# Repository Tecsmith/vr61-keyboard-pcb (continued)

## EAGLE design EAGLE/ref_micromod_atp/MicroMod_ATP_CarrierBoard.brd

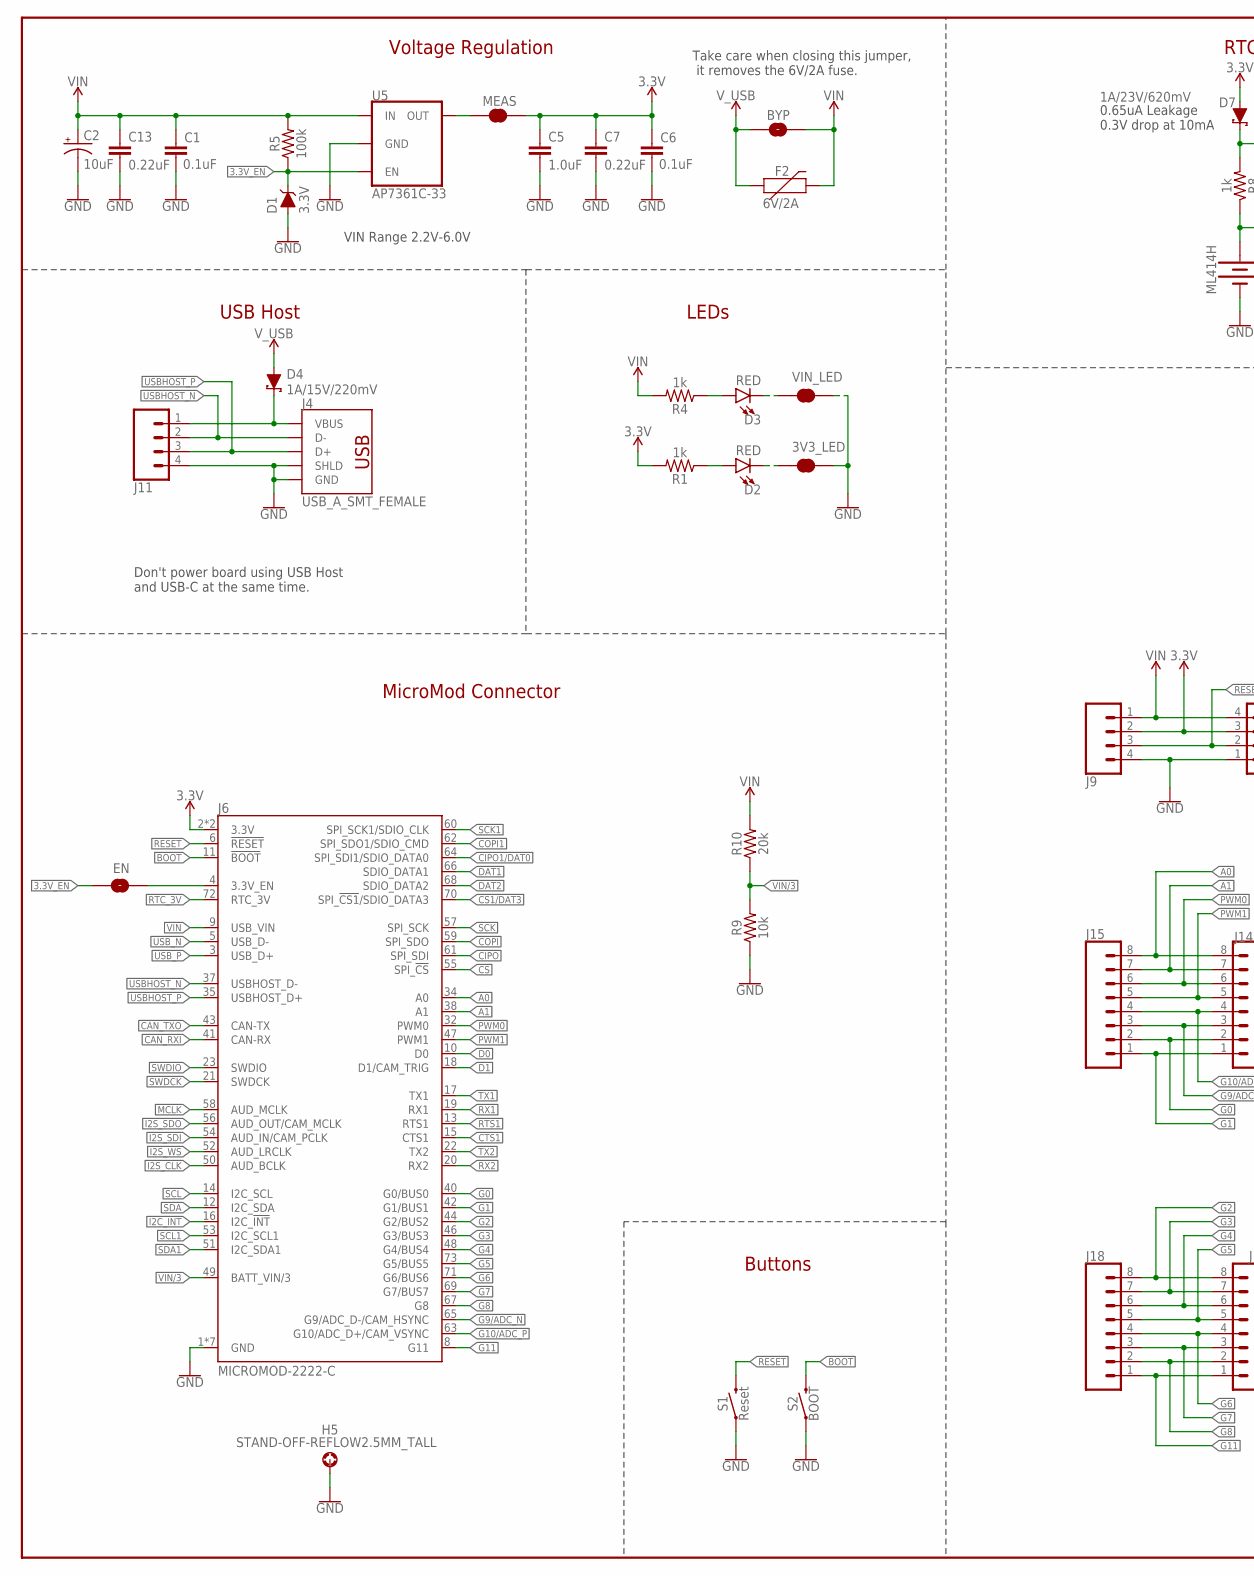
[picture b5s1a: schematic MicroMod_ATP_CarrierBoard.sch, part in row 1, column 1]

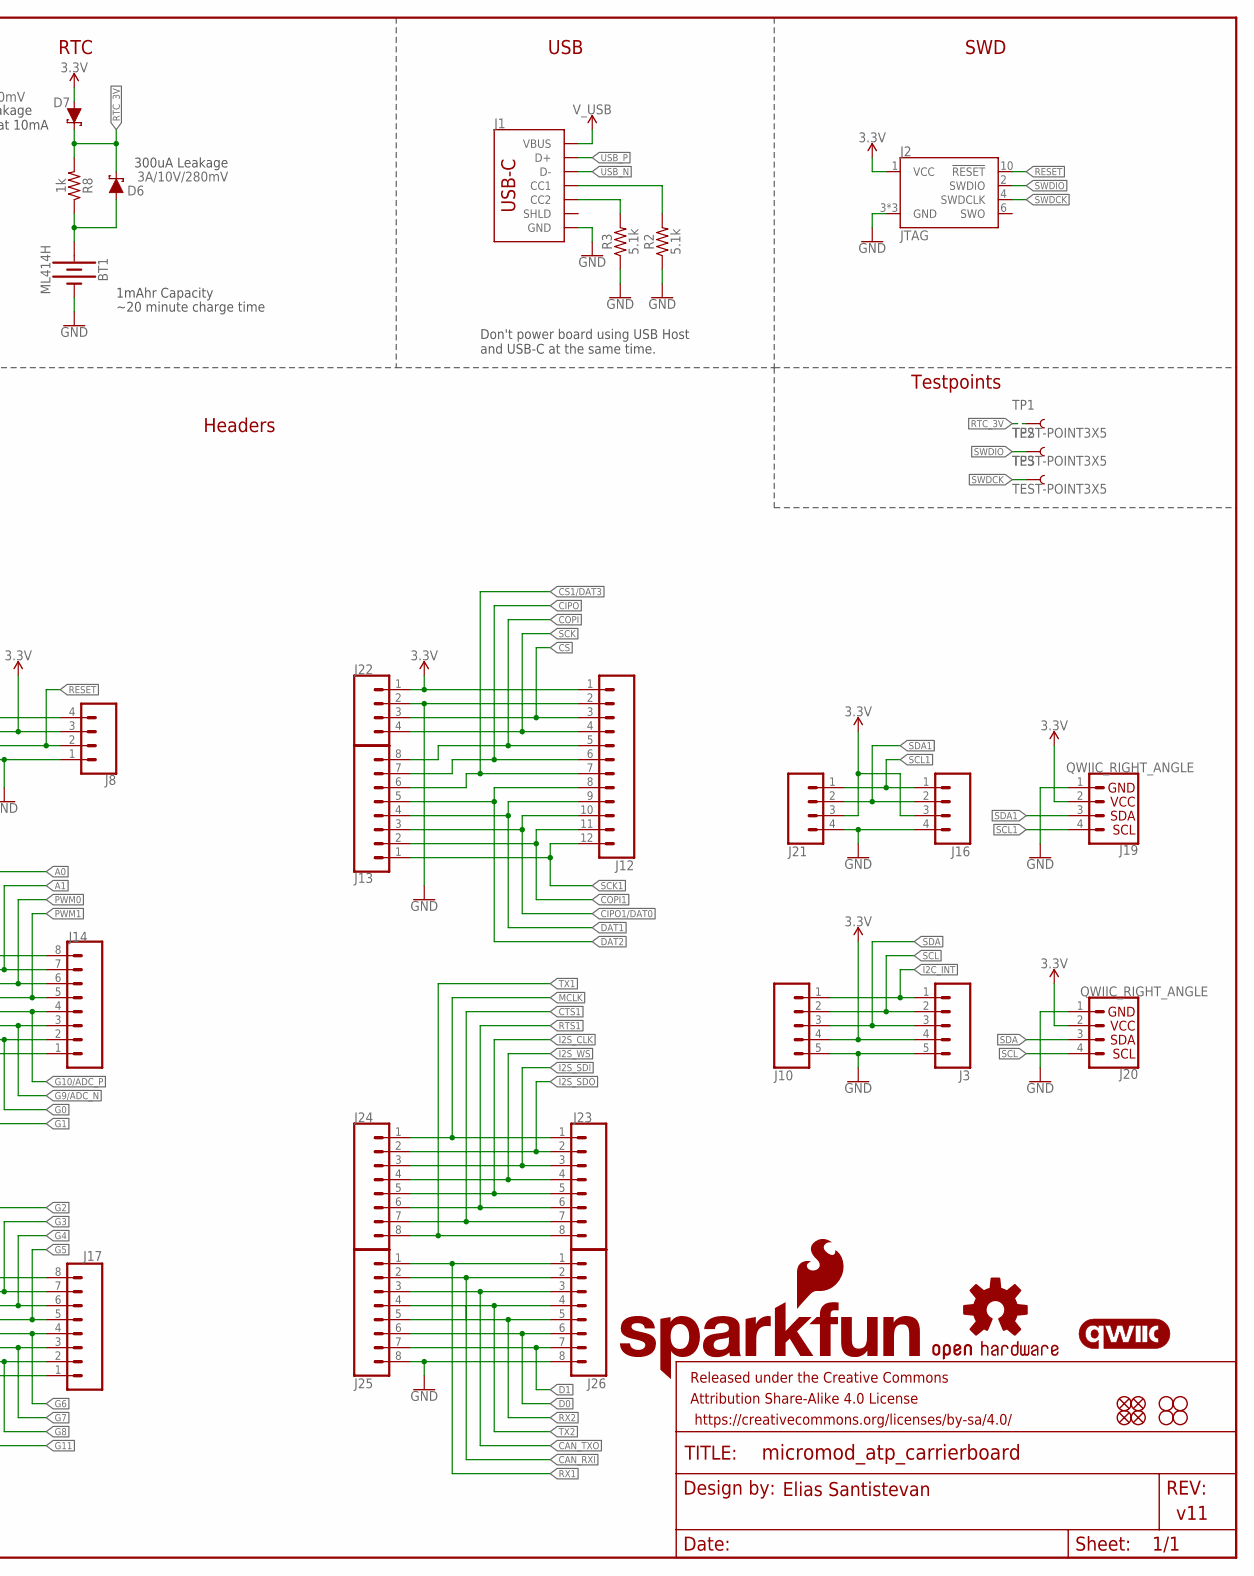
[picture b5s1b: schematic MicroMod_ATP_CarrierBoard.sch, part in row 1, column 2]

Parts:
3V3_LED: JUMPER-SMT_2_NC_TRACE_SILK; SMT-JUMPER_2_NC_TRACE_SILK
BT1: ML414H; ML414H_IV01E
BYP: JUMPER-SMT_2_NO_SILK; SMT-JUMPER_2_NO_SILK
C1, C6: 0.1uF; 0603
C2: 10uF; EIA3216
C5: 1.0uF; 0603
C7, C13: 0.22uF; 0603
D1: 3.3V; SOD-323
D2, D3: RED; LED-0603
D4: 1A/15V/220mV; DO-214BA
D6: 3A/10V/280mV; SOD-323
D7: 1A/23V/620mV; SOD-323
EN: JUMPER-SMT_2_NO_SILK; SMT-JUMPER_2_NO_SILK
F2: 6V/2A; 1210
FD1, FD2, FD3, FD4: FIDUCIALUFIDUCIAL; FIDUCIAL-MICRO
FRAME1: FRAME-LEDGER; CREATIVE_COMMONS
H1, H2, H3, H4: STAND-OFF
H5: STAND-OFF-REFLOW2.5MM_TALL; STAND-OFF-REFLOW-M2.5
J1: USB_C_2-LAYER_PADS; USB-C-16P-2LAYER-PADS
J2: JTAG; 2X5-PTH-1.27MM
J3: CONN_05NO_SILK; 1X05_NO_SILK
J4: USB_A_SMT_FEMALE; USB-A-S-SILK-FEMALE
J6: MICROMOD-2222-C; M.2-CONNECTOR-E
J8, J21: 1X04_SMD_STRAIGHT_COMBO; 1X04_SMD_VERTICAL_COMBO
J9: CONN_041X04_NO_SILK; 1X04_NO_SILK
J10: CONN_05VERT_FEMALE_HEADER; 1X05_SMD_VERTICAL_COMBO
J11, J16, J22: CONN_041X04_NO_SILK_NO_POP; 1X04_NO_SILK
J12: CONN_12SMD_COMBINED; 1X12_SMD_COMBINED
J13: CONN_08NO_SILK_DNP; 1X08_NO_SILK
J14, J17, J24, J25: CONN_08SMD-COMBO-FEMALE; 1X08_SMD_COMBINED
J15, J18, J23, J26: CONN_08NO_SILK_FEMALE_PTH; 1X08_NO_SILK
J19, J20: QWIIC_RIGHT_ANGLE; JST04_1MM_RA
LOGO1: SFE_LOGO_NAME_FLAME.1_INCH; SFE_LOGO_NAME_FLAME_.1
LOGO2: QWIIC_LOGO_5MM; QWIIC_5MM
LOGO3: OSHW-LOGOMINI; OSHW-LOGO-MINI
MEAS: JUMPER-COMBO_2_NC_TRACE; COMBO-JUMPER_2_NC_TRACE
R1, R4, R8: 1k; 0603
R2, R3: 5.1k; 0603
R5: 100k; 0603
R9: 10k; 0603
R10: 20k; 0603
S1: Reset; TACTILE_SWITCH_SMD_5.2MM
S2: BOOT; TACTILE_SWITCH_SMD_5.2MM
TP1, TP2, TP3: TEST-POINT3X5; PAD.03X.05
U5: AP7361C-33; UDFN-8
VIN_LED: JUMPER-SMT_2_NC_TRACE_SILK; SMT-JUMPER_2_NC_TRACE_SILK

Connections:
3.3V: C5.1, C6.1, C7.1, D7.A, J2.1 (VCC), J3.4, J6.2 (3.3V), J6.74 (3.3V), J8.3, J9.2, J10.4, J12.1, J16.3, J19.2, J20.2, J21.3, J22.1, MEAS.2, MEAS.4 (2), R1.2
3.3V_EN: D1.C, EN.1, R5.1, U5.5 (EN)
!BOOT!: J6.11 (!BOOT!), S2.3 (2), S2.4 (2)
!CS1!/DAT3: J6.70 (SPI_!CS1!/SDIO_DATA3), J12.7, J13.6
!CS!: J6.55 (SPI_!CS!), J12.3, J22.3
!RESET: J2.10 (!RESET), J6.6 (!RESET!), J8.2, J9.3, S1.3 (2), S1.4 (2)
A0: J6.34 (A0), J14.8, J15.8
A1: J6.38 (A1), J14.7, J15.7
CAN_RXI: J6.41 (CAN-RX), J25.2, J26.2
CAN_TXO: J6.43 (CAN-TX), J25.3, J26.3
CIPO: J6.61 (SPI_SDI), J12.6, J13.7
CIPO1/DAT0: J6.64 (SPI_SDI1/SDIO_DATA0), J12.10, J13.3
COPI: J6.59 (SPI_SDO), J12.5, J13.8
COPI1: J6.62 (SPI_SDO1/SDIO_CMD), J12.11, J13.2
CTS1: J6.15 (CTS1), J23.7, J24.7
D0: J6.10 (D0), J25.6, J26.6
D1: J6.18 (D1/CAM_TRIG), J25.7, J26.7
DAT1: J6.66 (SDIO_DATA1), J12.9, J13.4
DAT2: J6.68 (SDIO_DATA2), J12.8, J13.5
G0: J6.40 (G0/BUS0), J14.2, J15.2
G1: J6.42 (G1/BUS1), J14.1, J15.1
G2: J6.44 (G2/BUS2), J17.8, J18.8
G3: J6.46 (G3/BUS3), J17.7, J18.7
G4: J6.48 (G4/BUS4), J17.6, J18.6
G5: J6.73 (G5/BUS5), J17.5, J18.5
G6: J6.71 (G6/BUS6), J17.4, J18.4
G7: J6.69 (G7/BUS7), J17.3, J18.3
G8: J6.67 (G8), J17.2, J18.2
G9/ADC_N: J6.65 (G9/ADC_D-/CAM_HSYNC), J14.3, J15.3
G10/ADC_P: J6.63 (G10/ADC_D+/CAM_VSYNC), J14.4, J15.4
G11: J6.8 (G11), J17.1, J18.1
GND: 3V3_LED.2, BT1.-, C1.2, C2.-, C5.2, C6.2, C7.2, C13.2, D1.A, H5.1, J1.GND, J1.GND2 (GND), J2.3 (GND), J2.5 (GND), J2.9 (GND), J3.5, J4.GND, J4.SHLD1 (SHLD), J4.SHLD2 (SHLD), J6.1 (GND), J6.7 (GND), J6.33 (GND), J6.36 (GND), J6.39 (GND), J6.45 (GND), J6.75 (GND), J8.1, J9.4, J10.5, J11.4, J12.2, J16.4, J19.1, J20.1, J21.4, J22.2, J25.8, J26.8, R2.1, R3.1, R9.1, S1.1, S1.2 (1), S2.1, S2.2 (1), U5.4 (GND), U5.EP (GND), VIN_LED.2
I2C_!INT: J3.1, J6.16 (I2C_!INT!), J10.1
I2S_CLK: J6.50 (AUD_BCLK), J23.5, J24.5
I2S_SDI: J6.54 (AUD_IN/CAM_PCLK), J23.3, J24.3
I2S_SDO: J6.56 (AUD_OUT/CAM_MCLK), J23.2, J24.2
I2S_WS: J6.52 (AUD_LRCLK), J23.4, J24.4
MCLK: J6.58 (AUD_MCLK), J23.1, J24.1
unnamed: D2.A, R1.1
unnamed: D3.A, R4.1
unnamed: 3V3_LED.1, D2.C
unnamed: D3.C, VIN_LED.1
unnamed: EN.2, J6.4 (3.3V_EN)
unnamed: D4.C, J4.VBUS, J11.1
unnamed: J1.A5 (CC1), R2.2
unnamed: J1.B5 (CC2), R3.2
unnamed: BT1.+, D6.A, R8.1
OUT_MEAS: MEAS.1, MEAS.3 (1), U5.1 (OUT)
PWM0: J6.32 (PWM0), J14.6, J15.6
PWM1: J6.47 (PWM1), J14.5, J15.5
RTC_3V: D6.C, D7.C, J6.72 (RTC_3V), R8.2, TP1.P$1
RTS1: J6.13 (RTS1), J23.6, J24.6
RX1: J6.19 (RX1), J25.1, J26.1
RX2: J6.20 (RX2), J25.5, J26.5
SCK: J6.57 (SPI_SCK), J12.4, J22.4
SCK1: J6.60 (SPI_SCK1/SDIO_CLK), J12.12, J13.1
SCL: J3.2, J6.14 (I2C_SCL), J10.2, J20.4
SCL1: J6.53 (I2C_SCL1), J16.1, J19.4, J21.1
SDA: J3.3, J6.12 (I2C_SDA), J10.3, J20.3
SDA1: J6.51 (I2C_SDA1), J16.2, J19.3, J21.2
SWDCK: J2.4 (SWDCLK), J6.21 (SWDCK), TP3.P$1
SWDIO: J2.2 (SWDIO), J6.23 (SWDIO), TP2.P$1
TX1: J6.17 (TX1), J23.8, J24.8
TX2: J6.22 (TX2), J25.4, J26.4
USBHOST_N: J4.D-, J6.37 (USBHOST_D-), J11.2
USBHOST_P: J4.D+, J6.35 (USBHOST_D+), J11.3
USB_N: J1.A7 (D-), J1.B7 (D-), J6.5 (USB_D-)
USB_P: J1.A6 (D+), J1.B6 (D+), J6.3 (USB_D+)
VIN: BYP.2, C1.1, C2.+, C13.1, F2.2, J6.9 (USB_VIN), J8.4, J9.1, R4.2, R5.2, R10.2, U5.8 (IN)
VIN/3: J6.49 (BATT_VIN/3), R9.2, R10.1
V_USB: BYP.1, D4.A, F2.1, J1.VBUS1 (VBUS), J1.VBUS2 (VBUS)

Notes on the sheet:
300uA Leakage
0.65uA Leakage 0.3V drop at 10mA
~20 minute charge time
1mAhr Capacity
Take care when closing this jumper, it removes the 6V/2A fuse.
SWD
USB
Headers
RTC
Voltage Regulation
MicroMod Connector
Elias Santistevan
LEDs
USB Host
Buttons
v11
VIN Range 2.2V-6.0V
Don't power board using USB Host and USB-C at the same time.
Testpoints

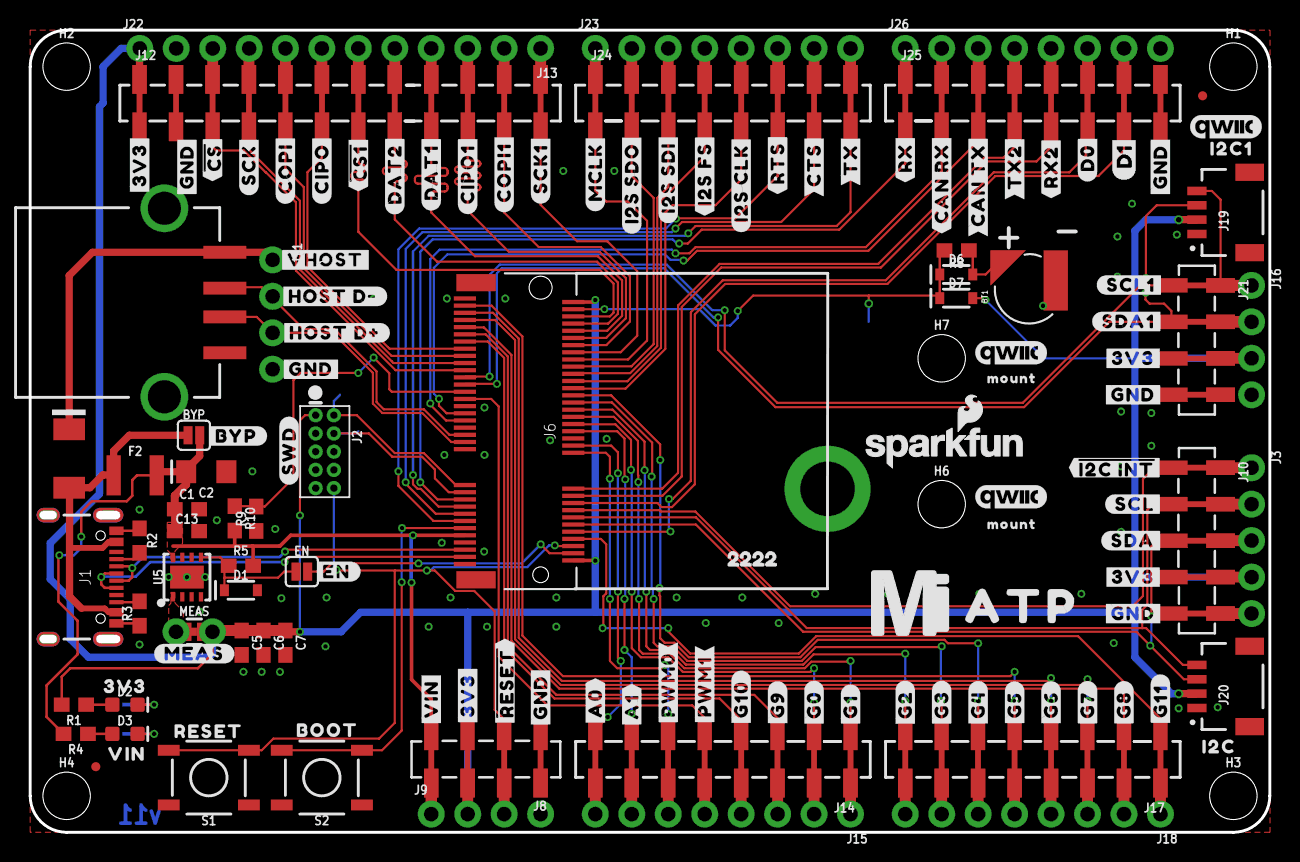
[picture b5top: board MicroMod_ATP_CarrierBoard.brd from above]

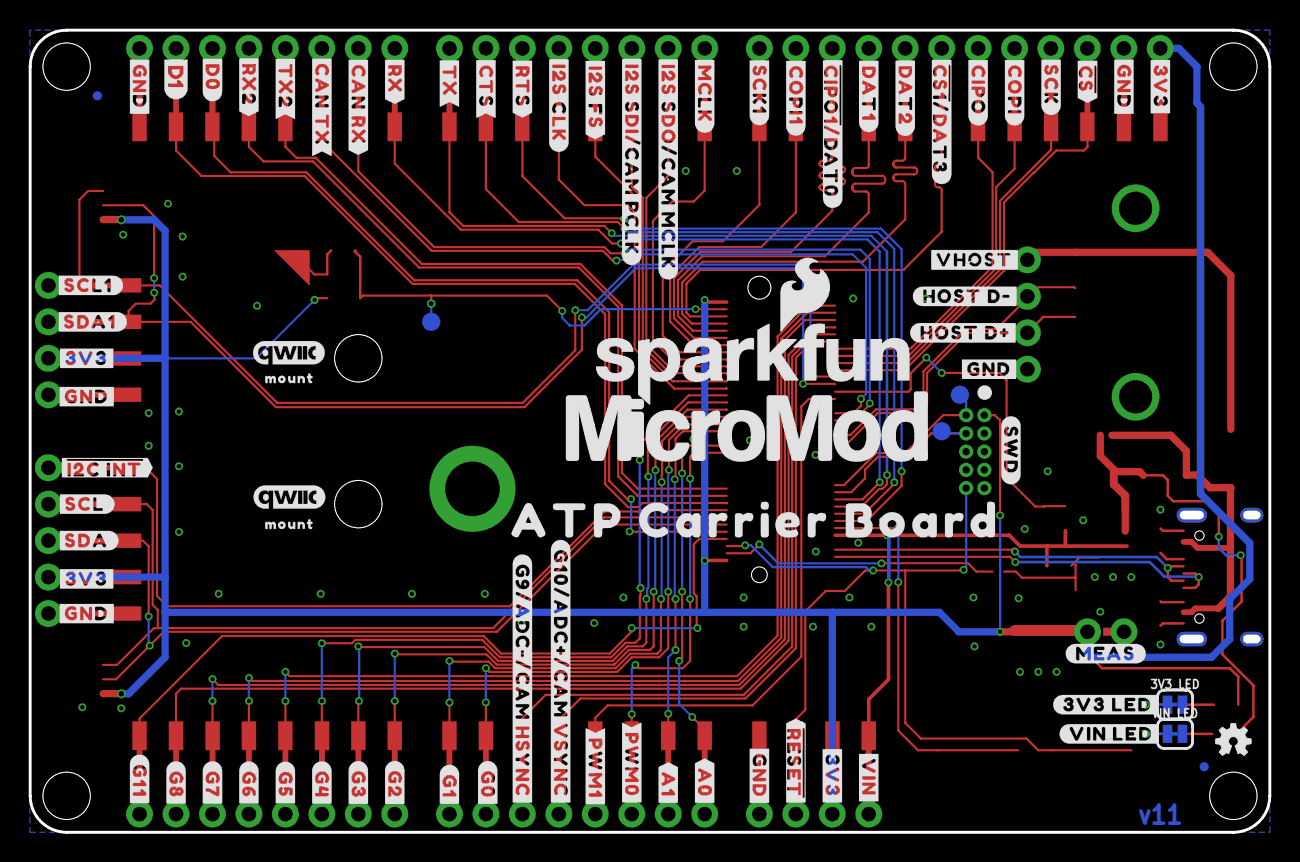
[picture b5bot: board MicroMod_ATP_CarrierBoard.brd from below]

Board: 2 copper layers, 86.0 x 55.5 mm, 222 parts (80 on the bottom side), 71 nets.

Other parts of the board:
H6, H7: STAND-OFF
LOGO4: SFE_LOGO_NAME_FLAME.2_INCH; SFE_LOGO_NAME_FLAME_.2
LOGO5, LOGO6, LOGO7, LOGO8: QWIIC_LOGO_3MM; QWIIC_5MM
U$1, U$123: #A0#10
U$2, U$124: #A1#10
U$3, U$27, U$46, U$47, U$58, U$89, U$100, U$101, U$102, U$103, U$104, U$105: #GND#0
U$4, U$120: #G0#2
U$5: #RESET10
U$6, U$98: #D0#0
U$7, U$119: #G1#2
U$8, U$118: #G2#2
U$9, U$117: #G3#3
U$10, U$116: #G4#4
U$11, U$115: #G5#5
U$12, U$114: #G6#6
U$13, U$113: #G7#7
U$14, U$112: #G8#8
U$15: #G9#9
U$16: #G10#10
U$17, U$111: #G11#10
U$18, U$121: #PWM0#10
U$19, U$122: #PWM1#10
U$20: ##CS1##5178039
U$21, U$110: ##I2C_INT##10
U$22: #CAN_RX#9
U$23, U$97: #CAN_TX#10
U$24: #CIPO#3
U$25: #COPI#2
U$26: #CTS#6
U$28: #SCK#2
U$29: #I2S_FS#5
U$30: #I2S_SDI#5
U$31: #I2S_SDO#5
U$32: #MCLK#4
U$33: #RTS#5
U$34: #RX#8
U$35: #TX#7
U$36: #DAT1#5178039
U$37, U$125: ##RESET##7
U$38, U$60, U$61, U$70, U$88, U$106, U$107, U$126: #3V3#1
U$39: #BYP#8
U$40, U$128: #HOST_D##9
U$41, U$129: #HOST_D##10
U$42, U$132: #MEAS#10
U$43: BOOT10
U$44, U$108: #SDA#4
U$45, U$127: #VIN#6
U$48: #EN#0
U$49, U$109: #SCL#5
U$50, U$146: #VHOST#0
U$51, U$131: #SWD#10
U$52: #I2S_CLK#5
U$53: #DAT2#5178039
U$54: #CIPO1#5178039
U$55: 22229
U$56: ##CIPO1##DAT0#5178038
U$57, U$75: #COPI1#2
U$59: ##CS##0
U$62: ATP0
U$63, U$76: #RX2#3
U$64, U$80: #TX2#2
U$65, U$78: #SCL1#3
U$66, U$79: #SDA1#3
U$67, U$77: #SCK1#2
U$68: VIN3
U$69: 3V34
U$71: I2C4
U$72: I2C14
U$73: ATP_CARRIER_BOARD1
U$81: ##CS##5178037
U$82: #DAT2#5
U$83: #DAT1#5
U$84: ##CS1##DAT3#5178037
U$85: #COPI#4
U$86: #SCK#4
U$87: #MCLK#6
U$90: #I2S_FS#7
U$91: #I2S_CLK#7
U$92: #RTS#7
U$93: #CTS#8
U$94: #TX#9
U$95: #RX#10
U$96: #CAN_RX#10
U$99, U$145: D10
U$133: #VIN_LED#10
U$134: #3V3_LED#10
U$135: #G9#ADC##CAM_HSYNC#9
U$136: #G10#ADC##CAM_VSYNC#10
U$137: #I2S_SDI#CAM_PCLK#7
U$138: #I2S_SDO#CAM_MCLK#7
U$139, U$141, U$142, U$143: MOUNT10
U$140: MICROMOD_MI_LOGO_1
U$144: MICROMOD_LOGO_1
U$147: #CIPO#5178038

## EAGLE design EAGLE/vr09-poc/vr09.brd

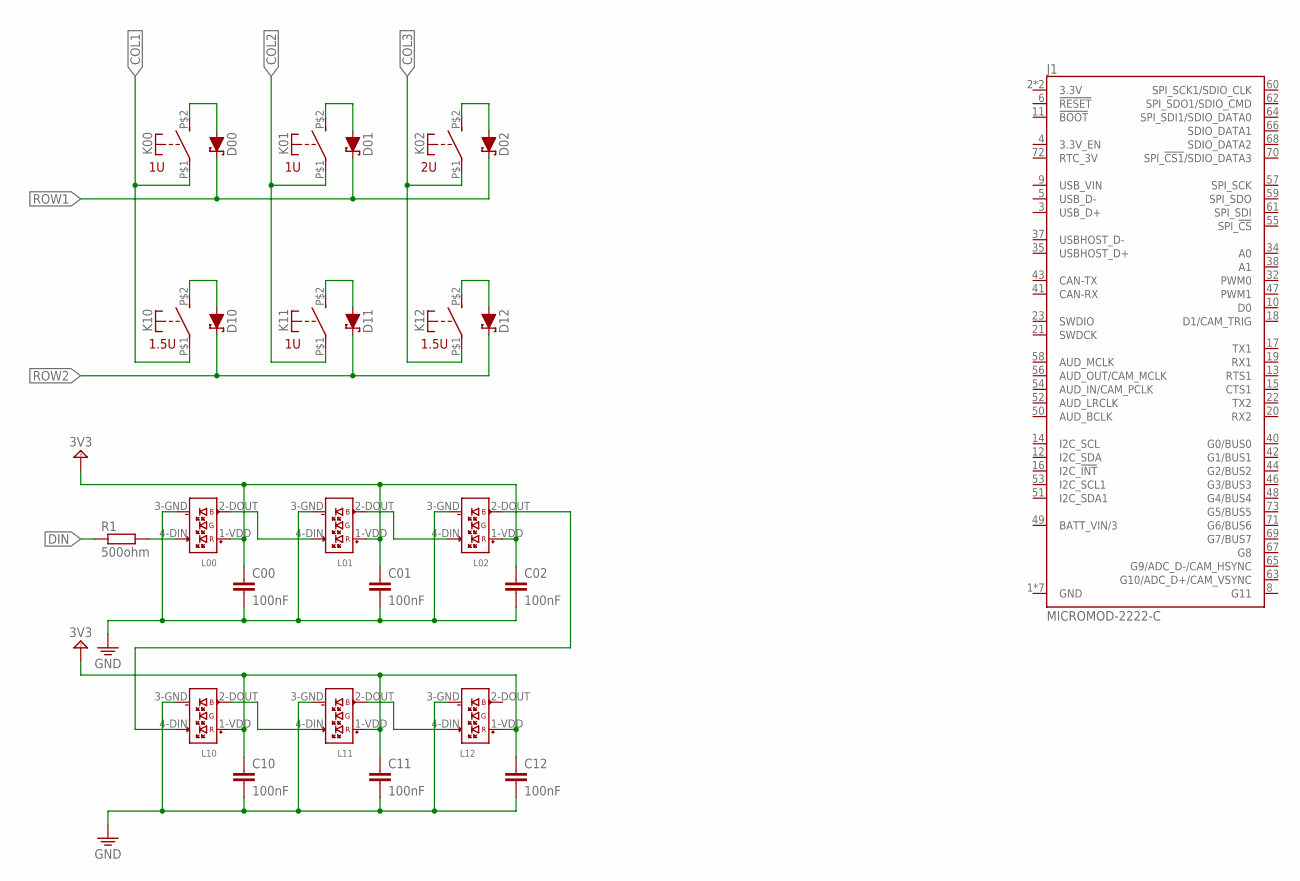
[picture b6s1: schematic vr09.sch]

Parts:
C00, C01, C02, C10, C11, C12: 100nF; C0603
D00, D01, D02, D10, D11, D12: 1N5819WS; SOD-123
J1: MICROMOD-2222-C; M.2-CONNECTOR-E
K00, K01, K02, K10, K11, K12: MX-5-PIN-HOTSWAP
L00, L01, L02, L10, L11, L12: SK6812-E-REVERSEDRILL; SK6812-E-DRILL
R1: 500ohm; R0603
U$1, U$2, U$5: MX-FPRINT-1905-100U
U$3: MX-FPRINT-1905-200U
U$4, U$6: MX-FPRINT-1905-150U

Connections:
COL1: K00.P$1, K10.P$1
COL2: K01.P$1, K11.P$1
COL3: K02.P$1, K12.P$1
DIN: R1.1
GND: C00.2, C01.2, C02.2, C10.2, C11.2, C12.2, L00.3-GND (3_GND), L01.3-GND (3_GND), L02.3-GND (3_GND), L10.3-GND (3_GND), L11.3-GND (3_GND), L12.3-GND (3_GND)
unnamed: D10.A, K10.P$2 (S)
unnamed: D11.A, K11.P$2 (S)
unnamed: D12.A, K12.P$2 (S)
unnamed: D02.A, K02.P$2 (S)
unnamed: D01.A, K01.P$2 (S)
unnamed: L00.4-DIN (4_DIN), R1.2
unnamed: D00.A, K00.P$2 (S)
unnamed: L00.2-DOUT (2_DOUT), L01.4-DIN (4_DIN)
unnamed: L01.2-DOUT (2_DOUT), L02.4-DIN (4_DIN)
unnamed: L11.2-DOUT (2_DOUT), L12.4-DIN (4_DIN)
unnamed: L10.2-DOUT (2_DOUT), L11.4-DIN (4_DIN)
unnamed: L02.2-DOUT (2_DOUT), L10.4-DIN (4_DIN)
ROW1: D00.C, D01.C, D02.C
ROW2: D10.C, D11.C, D12.C
VCC: C00.1, C01.1, C02.1, C10.1, C11.1, C12.1, L00.1-VDD (1_VDD), L01.1-VDD (1_VDD), L02.1-VDD (1_VDD), L10.1-VDD (1_VDD), L11.1-VDD (1_VDD), L12.1-VDD (1_VDD)

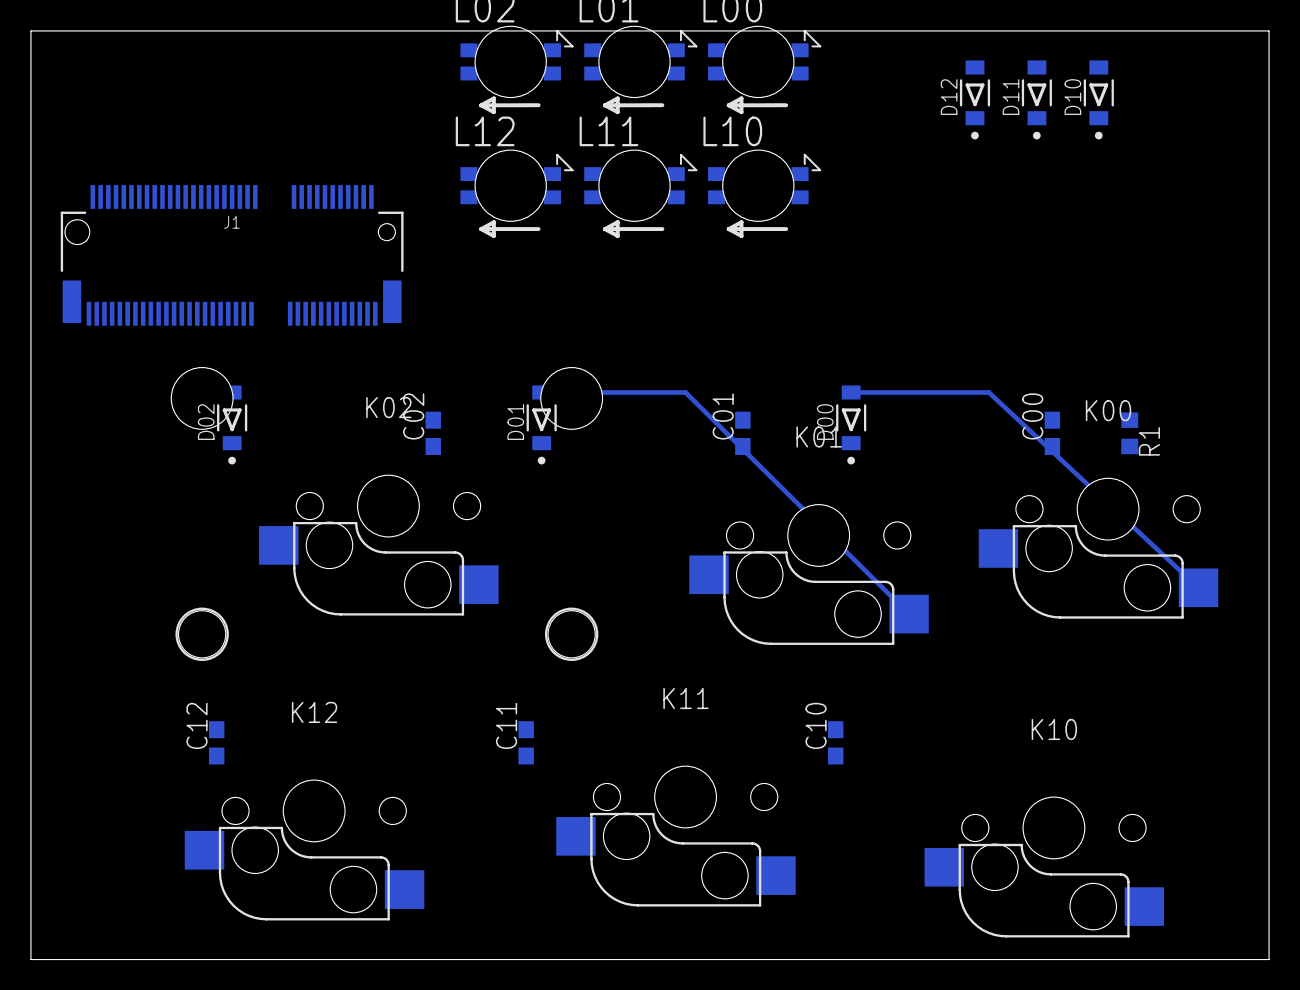
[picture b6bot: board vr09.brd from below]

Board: 2 copper layers, 80.0 x 60.0 mm, 33 parts (14 on the bottom side), 19 nets.

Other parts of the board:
U$7: MX-STABS-200U

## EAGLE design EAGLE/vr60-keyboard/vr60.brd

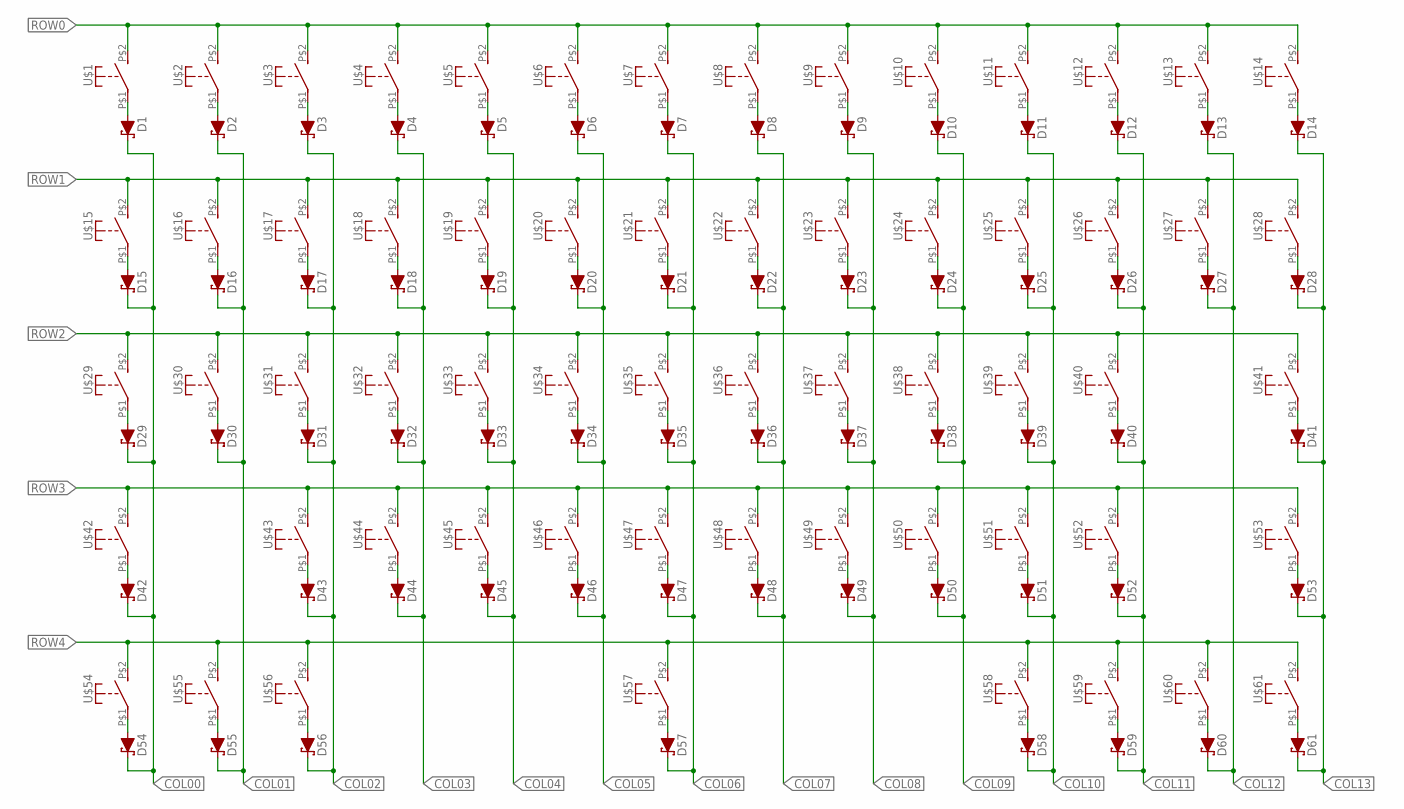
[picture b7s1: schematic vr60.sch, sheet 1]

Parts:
D1, D2, D3, D4, D5, D6, D7, D8, D9, D10, D11, D12, D13, D14, D15, D16, D17, D18, D19, D20, D21, D22, D23, D24, D25, D26, D27, D28, D29, D30, D31, D32, D33, D34, D35, D36, D37, D38, D39, D40, D41, D42, D43, D44, D45, D46, D47, D48, D49, D50, D51, D52, D53, D54, D55, D56, D57, D58, D59, D60, D61: 1N5819WS; SOD-123
U$1, U$2, U$3, U$4, U$5, U$6, U$7, U$8, U$9, U$10, U$11, U$12, U$13, U$14, U$15, U$16, U$17, U$18, U$19, U$20, U$21, U$22, U$23, U$24, U$25, U$26, U$27, U$28, U$29, U$30, U$31, U$32, U$33, U$34, U$35, U$36, U$37, U$38, U$39, U$40, U$41, U$42, U$43, U$44, U$45, U$46, U$47, U$48, U$49, U$50, U$51, U$52, U$53, U$54, U$55, U$56, U$57, U$58, U$59, U$60, U$61: MX-5-PIN-HOTSWAP

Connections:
COL00: D1.C, D15.C, D29.C, D42.C, D54.C
COL01: D2.C, D16.C, D30.C, D55.C
COL02: D3.C, D17.C, D31.C, D43.C, D56.C
COL03: D4.C, D18.C, D32.C, D44.C
COL04: D5.C, D19.C, D33.C, D45.C
COL05: D6.C, D20.C, D34.C, D46.C
COL06: D7.C, D21.C, D35.C, D47.C, D57.C
COL07: D8.C, D22.C, D36.C, D48.C
COL08: D9.C, D23.C, D37.C, D49.C
COL09: D10.C, D24.C, D38.C, D50.C
COL10: D11.C, D25.C, D39.C, D51.C, D58.C
COL11: D12.C, D26.C, D40.C, D52.C, D59.C
COL12: D13.C, D27.C, D60.C
COL13: D14.C, D28.C, D41.C, D53.C, D61.C
unnamed: D1.A, U$1.P$1
unnamed: D2.A, U$2.P$1
unnamed: D3.A, U$3.P$1
unnamed: D4.A, U$4.P$1
unnamed: D5.A, U$5.P$1
unnamed: D6.A, U$6.P$1
unnamed: D7.A, U$7.P$1
unnamed: D8.A, U$8.P$1
unnamed: D9.A, U$9.P$1
unnamed: D10.A, U$10.P$1
unnamed: D11.A, U$11.P$1
unnamed: D12.A, U$12.P$1
unnamed: D13.A, U$13.P$1
unnamed: D14.A, U$14.P$1
unnamed: D15.A, U$15.P$1
unnamed: D16.A, U$16.P$1
unnamed: D17.A, U$17.P$1
unnamed: D18.A, U$18.P$1
unnamed: D19.A, U$19.P$1
unnamed: D20.A, U$20.P$1
unnamed: D21.A, U$21.P$1
unnamed: D22.A, U$22.P$1
unnamed: D23.A, U$23.P$1
unnamed: D24.A, U$24.P$1
unnamed: D25.A, U$25.P$1
unnamed: D26.A, U$26.P$1
unnamed: D27.A, U$27.P$1
unnamed: D28.A, U$28.P$1
unnamed: D29.A, U$29.P$1
unnamed: D30.A, U$30.P$1
unnamed: D31.A, U$31.P$1
unnamed: D32.A, U$32.P$1
unnamed: D33.A, U$33.P$1
unnamed: D34.A, U$34.P$1
unnamed: D35.A, U$35.P$1
unnamed: D36.A, U$36.P$1
unnamed: D37.A, U$37.P$1
unnamed: D38.A, U$38.P$1
unnamed: D39.A, U$39.P$1
unnamed: D40.A, U$40.P$1
unnamed: D41.A, U$41.P$1
unnamed: D42.A, U$42.P$1
unnamed: D43.A, U$43.P$1
unnamed: D44.A, U$44.P$1
unnamed: D45.A, U$45.P$1
unnamed: D46.A, U$46.P$1
unnamed: D47.A, U$47.P$1
unnamed: D48.A, U$48.P$1
unnamed: D49.A, U$49.P$1
unnamed: D50.A, U$50.P$1
unnamed: D51.A, U$51.P$1
unnamed: D52.A, U$52.P$1
unnamed: D53.A, U$53.P$1
unnamed: D54.A, U$54.P$1
unnamed: D55.A, U$55.P$1
unnamed: D56.A, U$56.P$1
unnamed: D57.A, U$57.P$1
unnamed: D58.A, U$58.P$1
unnamed: D59.A, U$59.P$1
unnamed: D60.A, U$60.P$1
unnamed: D61.A, U$61.P$1
ROW0: U$1.P$2 (S), U$2.P$2 (S), U$3.P$2 (S), U$4.P$2 (S), U$5.P$2 (S), U$6.P$2 (S), U$7.P$2 (S), U$8.P$2 (S), U$9.P$2 (S), U$10.P$2 (S), U$11.P$2 (S), U$12.P$2 (S), U$13.P$2 (S), U$14.P$2 (S)
ROW1: U$15.P$2 (S), U$16.P$2 (S), U$17.P$2 (S), U$18.P$2 (S), U$19.P$2 (S), U$20.P$2 (S), U$21.P$2 (S), U$22.P$2 (S), U$23.P$2 (S), U$24.P$2 (S), U$25.P$2 (S), U$26.P$2 (S), U$27.P$2 (S), U$28.P$2 (S)
ROW2: U$29.P$2 (S), U$30.P$2 (S), U$31.P$2 (S), U$32.P$2 (S), U$33.P$2 (S), U$34.P$2 (S), U$35.P$2 (S), U$36.P$2 (S), U$37.P$2 (S), U$38.P$2 (S), U$39.P$2 (S), U$40.P$2 (S), U$41.P$2 (S)
ROW3: U$42.P$2 (S), U$43.P$2 (S), U$44.P$2 (S), U$45.P$2 (S), U$46.P$2 (S), U$47.P$2 (S), U$48.P$2 (S), U$49.P$2 (S), U$50.P$2 (S), U$51.P$2 (S), U$52.P$2 (S), U$53.P$2 (S)
ROW4: U$54.P$2 (S), U$55.P$2 (S), U$56.P$2 (S), U$57.P$2 (S), U$58.P$2 (S), U$59.P$2 (S), U$60.P$2 (S), U$61.P$2 (S)

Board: 2 copper layers, 122 parts (0 on the bottom side), 80 nets, no tracks yet.

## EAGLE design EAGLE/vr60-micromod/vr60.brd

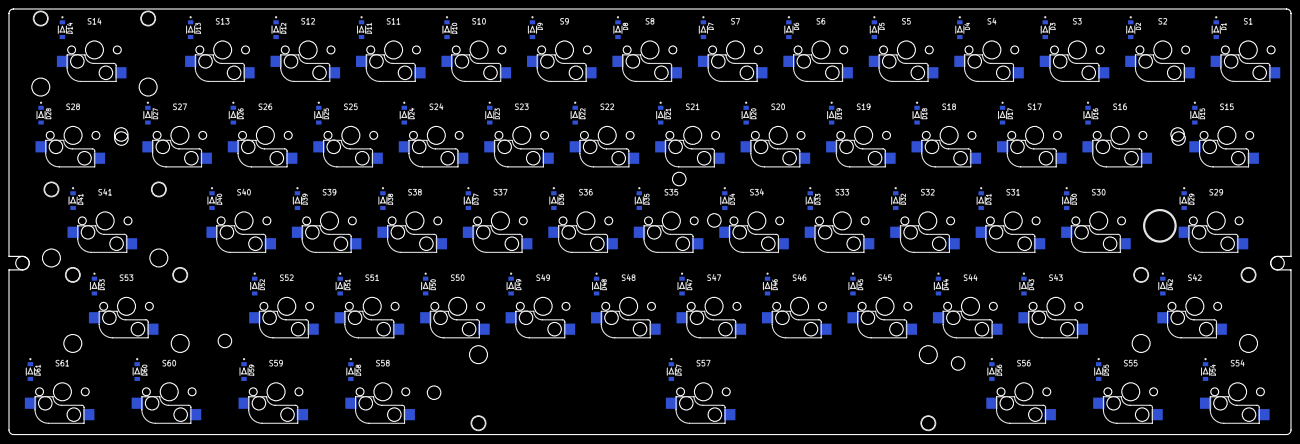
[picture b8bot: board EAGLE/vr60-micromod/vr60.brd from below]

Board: 2 copper layers, 285.0 x 94.6 mm, 188 parts (61 on the bottom side), 80 nets, no tracks yet.

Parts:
B14, B41, B42, B53: MX-STABS-200U
B57: MX-STABS-625U
D1, D2, D3, D4, D5, D6, D7, D8, D9, D10, D11, D12, D13, D14, D15, D16, D17, D18, D19, D20, D21, D22, D23, D24, D25, D26, D27, D28, D29, D30, D31, D32, D33, D34, D35, D36, D37, D38, D39, D40, D41, D42, D43, D44, D45, D46, D47, D48, D49, D50, D51, D52, D53, D54, D55, D56, D57, D58, D59, D60, D61: SOD-123
S1, S2, S3, S4, S5, S6, S7, S8, S9, S10, S11, S12, S13, S14, S15, S16, S17, S18, S19, S20, S21, S22, S23, S24, S25, S26, S27, S28, S29, S30, S31, S32, S33, S34, S35, S36, S37, S38, S39, S40, S41, S42, S43, S44, S45, S46, S47, S48, S49, S50, S51, S52, S53, S54, S55, S56, S57, S58, S59, S60, S61: MX-5-PIN-HOTSWAP
Z1, Z2, Z3, Z4, Z5, Z6, Z7, Z8, Z9, Z10, Z11, Z12, Z13, Z16, Z17, Z18, Z19, Z20, Z21, Z22, Z23, Z24, Z25, Z26, Z27, Z30, Z31, Z32, Z33, Z34, Z35, Z36, Z37, Z38, Z39, Z40, Z43, Z44, Z45, Z46, Z47, Z48, Z49, Z50, Z51, Z52: MX-FPRINT-100U19; MX-FPRINT-1900-100U
Z14: MX-FPRINT-200U19; MX-FPRINT-1900-200U
Z15, Z28: MX-FPRINT-150U19; MX-FPRINT-1900-150U
Z29: MX-FPRINT-175U19; MX-FPRINT-1900-175U
Z41, Z42: MX-FPRINT-225U19; MX-FPRINT-1900-225U
Z53: MX-FPRINT-275U19; MX-FPRINT-1900-275U
Z54, Z55, Z56, Z58, Z59, Z60, Z61: MX-FPRINT-125U19; MX-FPRINT-1900-125U
Z57: MX-FPRINT-625U19; MX-FPRINT-1900-625U

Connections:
COL0: D1.C, D15.C, D29.C, D42.C, D54.C
COL1: D2.C, D16.C, D30.C, D55.C
COL2: D3.C, D17.C, D31.C, D43.C, D56.C
COL3: D4.C, D18.C, D32.C, D44.C
COL4: D5.C, D19.C, D33.C, D45.C
COL5: D6.C, D20.C, D34.C, D46.C
COL6: D7.C, D21.C, D35.C, D47.C, D57.C
COL7: D8.C, D22.C, D36.C, D48.C
COL8: D9.C, D23.C, D37.C, D49.C
COL9: D10.C, D24.C, D38.C, D50.C
COL10: D11.C, D25.C, D39.C, D51.C, D58.C
COL11: D12.C, D26.C, D40.C, D52.C, D59.C
COL12: D13.C, D27.C, D60.C
COL13: D14.C, D28.C, D41.C, D53.C, D61.C
unnamed: D1.A, S1.P$1
unnamed: D2.A, S2.P$1
unnamed: D3.A, S3.P$1
unnamed: D4.A, S4.P$1
unnamed: D5.A, S5.P$1
unnamed: D6.A, S6.P$1
unnamed: D7.A, S7.P$1
unnamed: D8.A, S8.P$1
unnamed: D9.A, S9.P$1
unnamed: D10.A, S10.P$1
unnamed: D11.A, S11.P$1
unnamed: D12.A, S12.P$1
unnamed: D13.A, S13.P$1
unnamed: D14.A, S14.P$1
unnamed: D15.A, S15.P$1
unnamed: D16.A, S16.P$1
unnamed: D17.A, S17.P$1
unnamed: D18.A, S18.P$1
unnamed: D19.A, S19.P$1
unnamed: D20.A, S20.P$1
unnamed: D21.A, S21.P$1
unnamed: D22.A, S22.P$1
unnamed: D23.A, S23.P$1
unnamed: D24.A, S24.P$1
unnamed: D25.A, S25.P$1
unnamed: D26.A, S26.P$1
unnamed: D27.A, S27.P$1
unnamed: D28.A, S28.P$1
unnamed: D29.A, S29.P$1
unnamed: D30.A, S30.P$1
unnamed: D31.A, S31.P$1
unnamed: D32.A, S32.P$1
unnamed: D33.A, S33.P$1
unnamed: D34.A, S34.P$1
unnamed: D35.A, S35.P$1
unnamed: D36.A, S36.P$1
unnamed: D37.A, S37.P$1
unnamed: D38.A, S38.P$1
unnamed: D39.A, S39.P$1
unnamed: D40.A, S40.P$1
unnamed: D41.A, S41.P$1
unnamed: D42.A, S42.P$1
unnamed: D43.A, S43.P$1
unnamed: D44.A, S44.P$1
unnamed: D45.A, S45.P$1
unnamed: D46.A, S46.P$1
unnamed: D47.A, S47.P$1
unnamed: D48.A, S48.P$1
unnamed: D49.A, S49.P$1
unnamed: D50.A, S50.P$1
unnamed: D51.A, S51.P$1
unnamed: D52.A, S52.P$1
unnamed: D53.A, S53.P$1
unnamed: D54.A, S54.P$1
unnamed: D55.A, S55.P$1
unnamed: D56.A, S56.P$1
unnamed: D57.A, S57.P$1
unnamed: D58.A, S58.P$1
unnamed: D59.A, S59.P$1
unnamed: D60.A, S60.P$1
unnamed: D61.A, S61.P$1
ROW0: S1.P$2, S2.P$2, S3.P$2, S4.P$2, S5.P$2, S6.P$2, S7.P$2, S8.P$2, S9.P$2, S10.P$2, S11.P$2, S12.P$2, S13.P$2, S14.P$2
ROW1: S15.P$2, S16.P$2, S17.P$2, S18.P$2, S19.P$2, S20.P$2, S21.P$2, S22.P$2, S23.P$2, S24.P$2, S25.P$2, S26.P$2, S27.P$2, S28.P$2
ROW2: S29.P$2, S30.P$2, S31.P$2, S32.P$2, S33.P$2, S34.P$2, S35.P$2, S36.P$2, S37.P$2, S38.P$2, S39.P$2, S40.P$2, S41.P$2
ROW3: S42.P$2, S43.P$2, S44.P$2, S45.P$2, S46.P$2, S47.P$2, S48.P$2, S49.P$2, S50.P$2, S51.P$2, S52.P$2, S53.P$2
ROW4: S54.P$2, S55.P$2, S56.P$2, S57.P$2, S58.P$2, S59.P$2, S60.P$2, S61.P$2

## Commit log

2022-01-18 summary
2022-01-30 upload ref dims
2022-02-04 add kailh hotswap spec
2022-02-04 initial and empty
2022-02-05 initial footprint
2022-02-08 more specs
2022-02-11 more docs
2022-05-21 redo VIA json
2022-05-21 rename
2022-05-21 RP2040 docs
2022-05-22 sort docs
2022-05-31 additional protection & diode placements
2022-06-04 pcb tracing done
2022-06-05 added heat sink on 1117
2022-06-05 wip, logos
2022-06-06 logos and text
2022-06-06 renames
2022-06-06 i think it's ready
2022-06-06 correct micromod logo
2022-06-06 updates after peer review on qmk discord
2022-06-06 minor edit to sch pdf
2022-06-07 updated images
2022-06-12 added LED caps
2022-06-13 turned top row around
2022-06-15 production ready
2022-06-17 production ready, rev B
2022-06-17 forgot ratsnest
2022-06-17 pcbway sponsoring first prototype build
2022-06-17 thank you pcbway
2022-06-18 update udb
2022-06-18 file renames
2022-06-18 not mine to host
2022-06-19 updates to docs
2022-06-28 update updates
2022-07-20 FAIL!
2022-07-20 wip 2022-07-20
2022-07-21 wip 2022-07-21
2022-07-22 wip 2022-07-22
2022-08-27 final touches and validation for rev B
2022-08-27 updated screenshots
2022-08-28 updates after production prep
2022-08-30 move r8 + final rev B production files
2022-08-31 bom fix
2022-09-24 74AHCT1G125GW
2022-10-21 adjust centre ap2 drill hole
2022-10-30 minor edits
2024-09-17 Reb B.2 update
2024-09-18 Boot switch redo
2024-09-18 Moved license to CC BY-SA 4.0
2024-09-20 Added Bakeneko footprint
2024-12-21 Rev C
